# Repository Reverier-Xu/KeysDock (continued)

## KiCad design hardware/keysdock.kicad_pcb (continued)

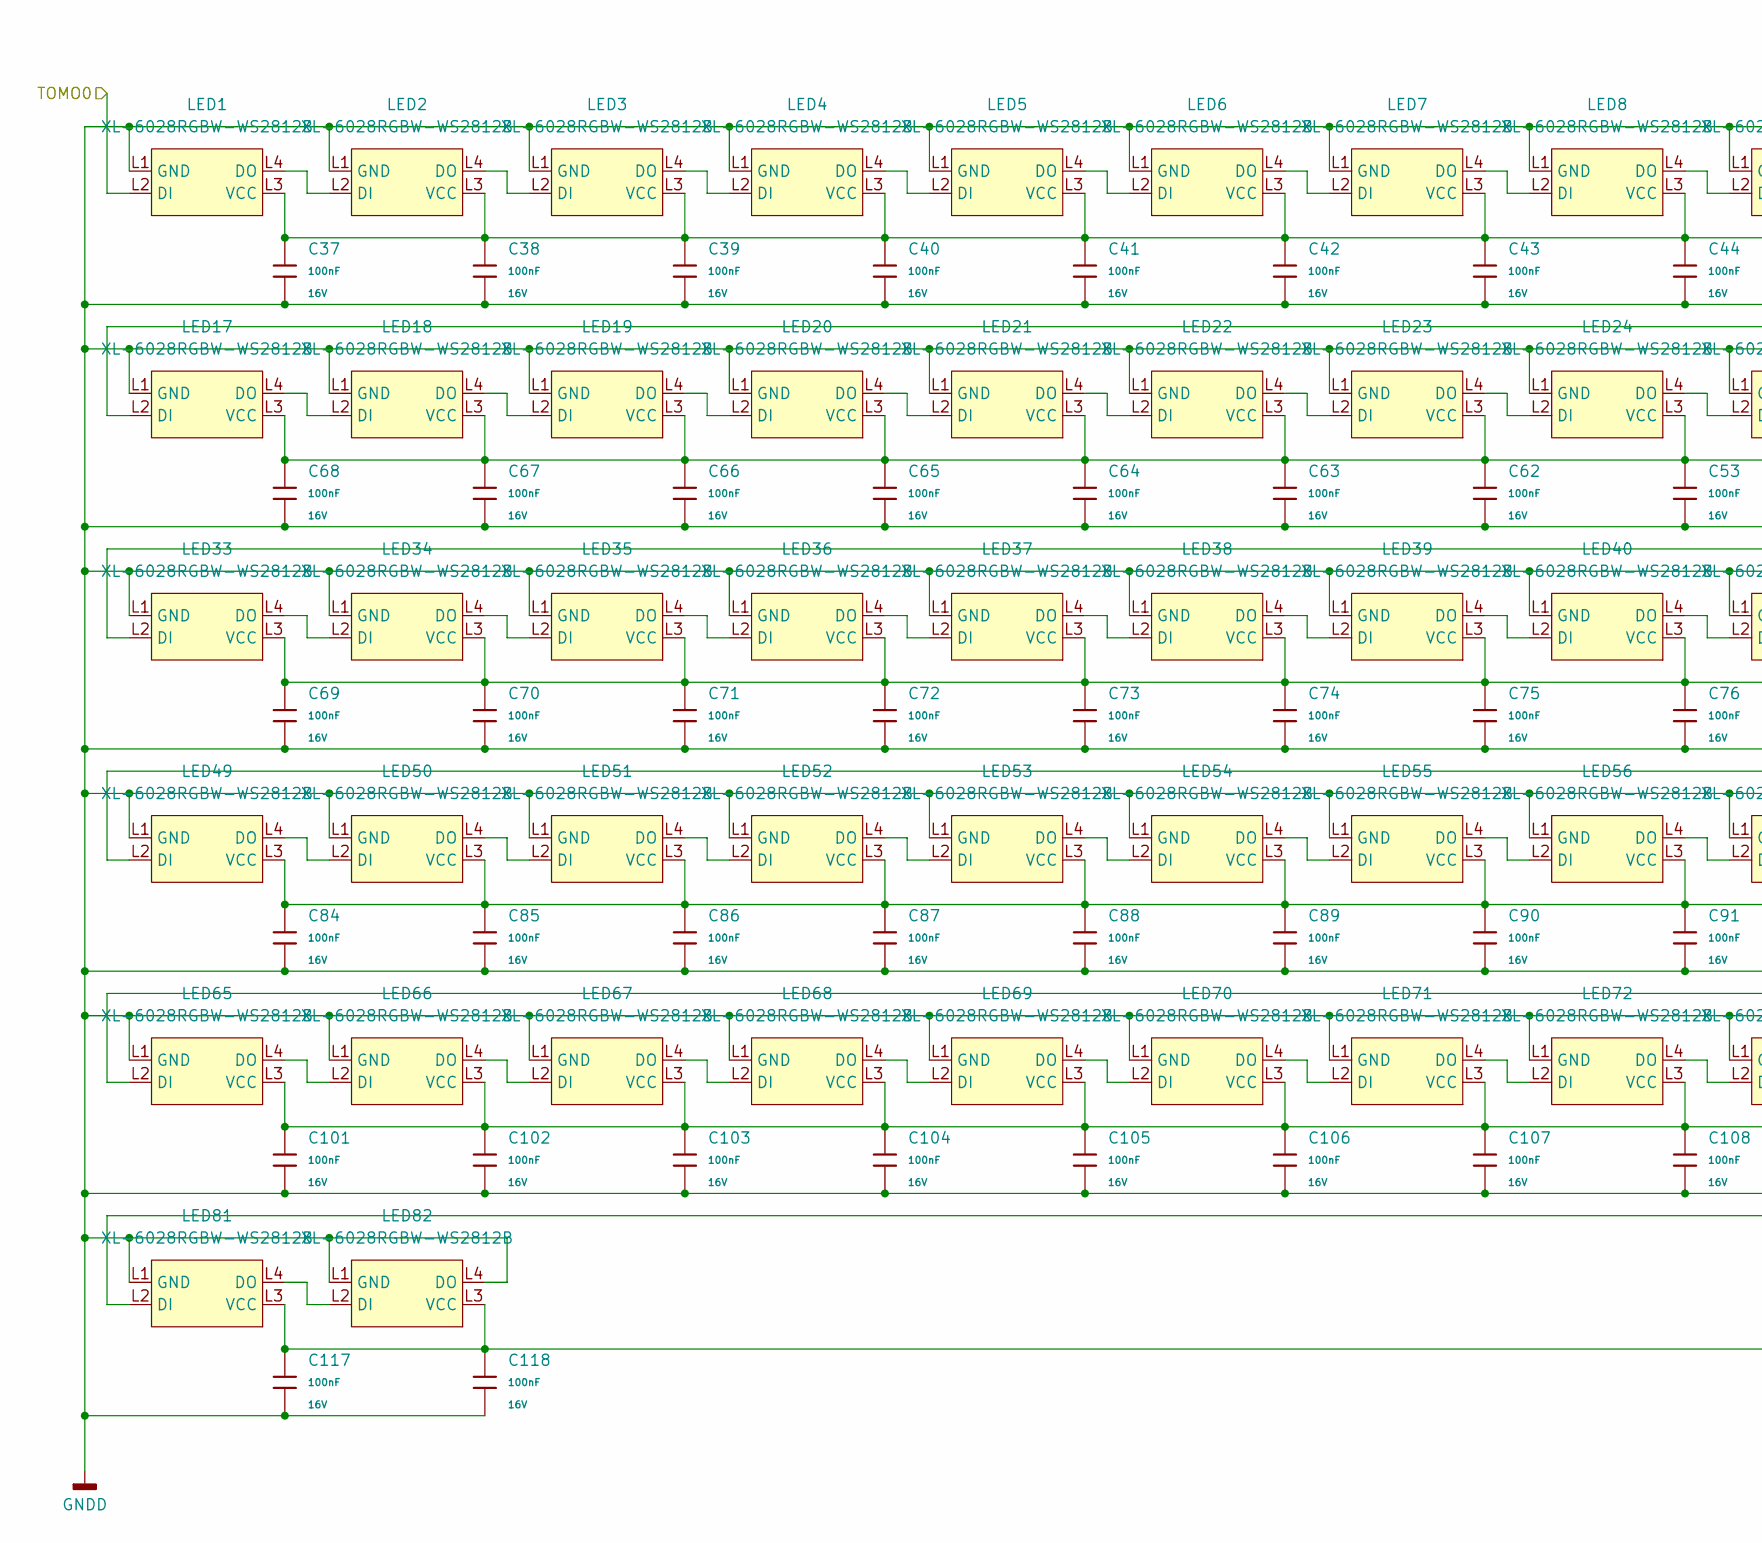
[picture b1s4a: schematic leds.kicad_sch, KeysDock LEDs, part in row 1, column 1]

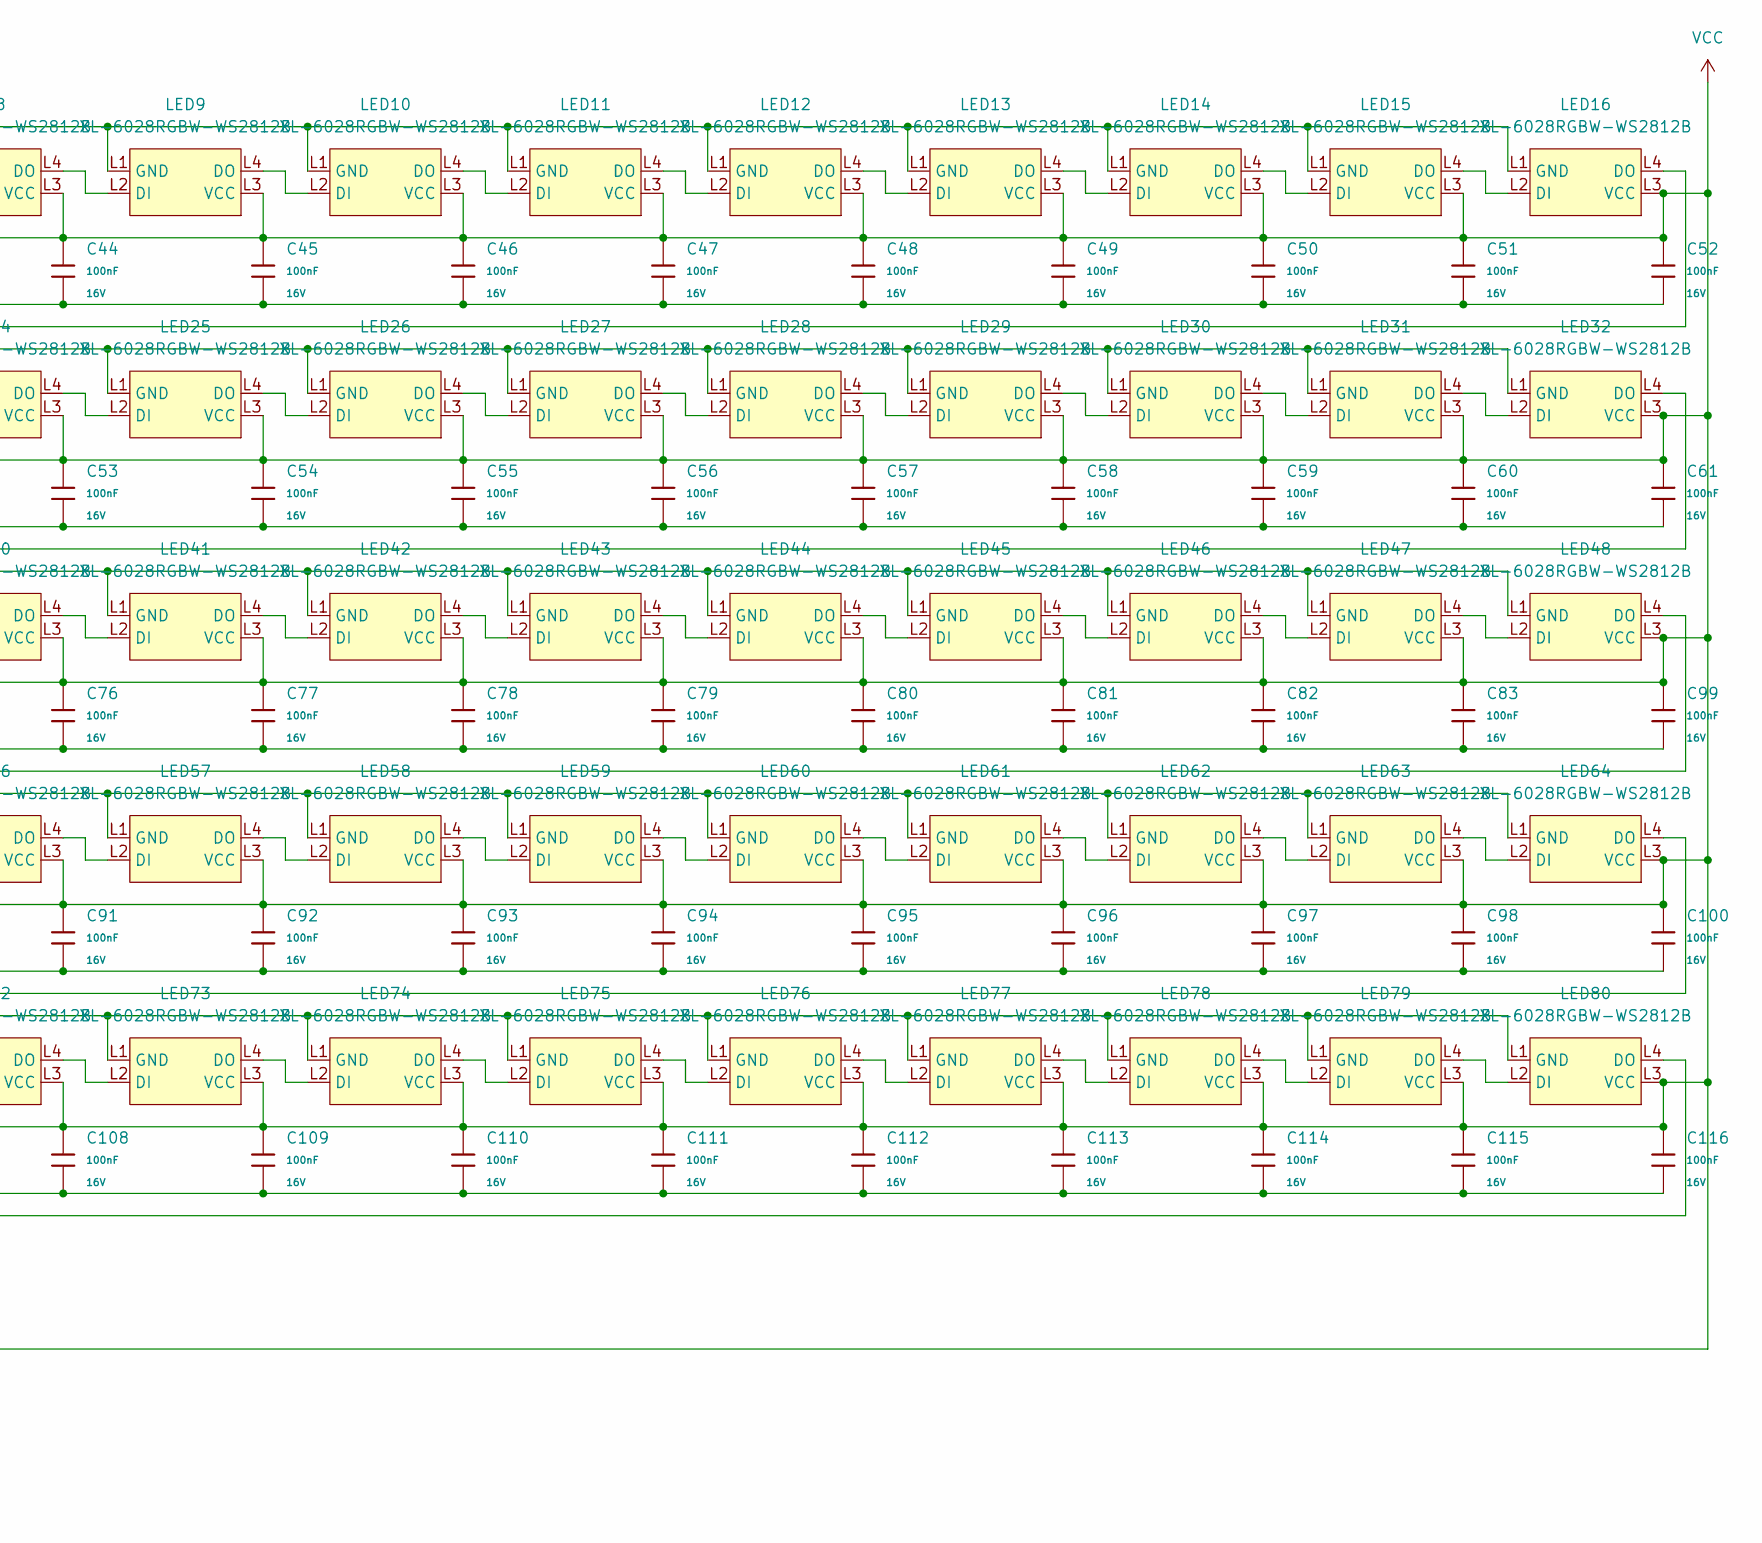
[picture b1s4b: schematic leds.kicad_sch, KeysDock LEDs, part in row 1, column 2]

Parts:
C37, C38, C39, C40, C41, C42, C43, C44, C45, C46, C47, C48, C49, C50, C51, C52, C53, C54, C55, C56, C57, C58, C59, C60, C61, C62, C63, C64, C65, C66, C67, C68, C69, C70, C71, C72, C73, C74, C75, C76, C77, C78, C79, C80, C81, C82, C83, C84, C85, C86, C87, C88, C89, C90, C91, C92, C93, C94, C95, C96, C97, C98, C99, C100, C101, C102, C103, C104, C105, C106, C107, C108, C109, C110, C111, C112, C113, C114, C115, C116, C117, C118: 100nF; C_0402; Voltage Rated 16V; Tolerance ±10%; Part CL05B104KO5NNNC; LCSC C1525
LED1, LED2, LED3, LED4, LED5, LED6, LED7, LED8, LED9, LED10, LED11, LED12, LED13, LED14, LED15, LED16, LED17, LED18, LED19, LED20, LED21, LED22, LED23, LED24, LED25, LED26, LED27, LED28, LED29, LED30, LED31, LED32, LED33, LED34, LED35, LED36, LED37, LED38, LED39, LED40, LED41, LED42, LED43, LED44, LED45, LED46, LED47, LED48, LED49, LED50, LED51, LED52, LED53, LED54, LED55, LED56, LED57, LED58, LED59, LED60, LED61, LED62, LED63, LED64, LED65, LED66, LED67, LED68, LED69, LED70, LED71, LED72, LED73, LED74, LED75, LED76, LED77, LED78, LED79, LED80, LED81, LED82: XL-6028RGBW-WS2812B; LCSC C42163197

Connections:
/leds/TOMO0: LED1.L2 (DI); also elsewhere on the board
GNDD: C37.2, C38.2, C39.2, C40.2, C41.2, C42.2, C43.2, C44.2, C45.2, C46.2, C47.2, C48.2, C49.2, C50.2, C51.2, C52.2, C53.2, C54.2, C55.2, C56.2, C57.2, C58.2, C59.2, C60.2, C61.2, C62.2, C63.2, C64.2, C65.2, C66.2, C67.2, C68.2, C69.2, C70.2, C71.2, C72.2, C73.2, C74.2, C75.2, C76.2, C77.2, C78.2, C79.2, C80.2, C81.2, C82.2, C83.2, C84.2, C85.2, C86.2, C87.2, C88.2, C89.2, C90.2, C91.2, C92.2, C93.2, C94.2, C95.2, C96.2, C97.2, C98.2, C99.2, C100.2, C101.2, C102.2, C103.2, C104.2, C105.2, C106.2, C107.2, C108.2, C109.2, C110.2, C111.2, C112.2, C113.2, C114.2, C115.2, C116.2, C117.2, C118.2, LED1.L1 (GND), LED2.L1 (GND), LED3.L1 (GND), LED4.L1 (GND), LED5.L1 (GND), LED6.L1 (GND), LED7.L1 (GND), LED8.L1 (GND), LED9.L1 (GND), LED10.L1 (GND), LED11.L1 (GND), LED12.L1 (GND), LED13.L1 (GND), LED14.L1 (GND), LED15.L1 (GND), LED16.L1 (GND), LED17.L1 (GND), LED18.L1 (GND), LED19.L1 (GND), LED20.L1 (GND), LED21.L1 (GND), LED22.L1 (GND), LED23.L1 (GND), LED24.L1 (GND), LED25.L1 (GND), LED26.L1 (GND), LED27.L1 (GND), LED28.L1 (GND), LED29.L1 (GND), LED30.L1 (GND), LED31.L1 (GND), LED32.L1 (GND), LED33.L1 (GND), LED34.L1 (GND), LED35.L1 (GND), LED36.L1 (GND), LED37.L1 (GND), LED38.L1 (GND), LED39.L1 (GND), LED40.L1 (GND), LED41.L1 (GND), LED42.L1 (GND), LED43.L1 (GND), LED44.L1 (GND), LED45.L1 (GND), LED46.L1 (GND), LED47.L1 (GND), LED48.L1 (GND), LED49.L1 (GND), LED50.L1 (GND), LED51.L1 (GND), LED52.L1 (GND), LED53.L1 (GND), LED54.L1 (GND), LED55.L1 (GND), LED56.L1 (GND), LED57.L1 (GND), LED58.L1 (GND), LED59.L1 (GND), LED60.L1 (GND), LED61.L1 (GND), LED62.L1 (GND), LED63.L1 (GND), LED64.L1 (GND), LED65.L1 (GND), LED66.L1 (GND), LED67.L1 (GND), LED68.L1 (GND), LED69.L1 (GND), LED70.L1 (GND), LED71.L1 (GND), LED72.L1 (GND), LED73.L1 (GND), LED74.L1 (GND), LED75.L1 (GND), LED76.L1 (GND), LED77.L1 (GND), LED78.L1 (GND), LED79.L1 (GND), LED80.L1 (GND), LED81.L1 (GND), LED82.L1 (GND), LED82.L4 (DO); also elsewhere on the board
unnamed: LED1.L4 (DO), LED2.L2 (DI)
unnamed: LED2.L4 (DO), LED3.L2 (DI)
unnamed: LED3.L4 (DO), LED4.L2 (DI)
unnamed: LED4.L4 (DO), LED5.L2 (DI)
unnamed: LED5.L4 (DO), LED6.L2 (DI)
unnamed: LED6.L4 (DO), LED7.L2 (DI)
unnamed: LED7.L4 (DO), LED8.L2 (DI)
unnamed: LED8.L4 (DO), LED9.L2 (DI)
unnamed: LED9.L4 (DO), LED10.L2 (DI)
unnamed: LED10.L4 (DO), LED11.L2 (DI)
unnamed: LED11.L4 (DO), LED12.L2 (DI)
unnamed: LED12.L4 (DO), LED13.L2 (DI)
unnamed: LED13.L4 (DO), LED14.L2 (DI)
unnamed: LED14.L4 (DO), LED15.L2 (DI)
unnamed: LED15.L4 (DO), LED16.L2 (DI)
unnamed: LED16.L4 (DO), LED17.L2 (DI)
unnamed: LED17.L4 (DO), LED18.L2 (DI)
unnamed: LED18.L4 (DO), LED19.L2 (DI)
unnamed: LED19.L4 (DO), LED20.L2 (DI)
unnamed: LED20.L4 (DO), LED21.L2 (DI)
unnamed: LED21.L4 (DO), LED22.L2 (DI)
unnamed: LED22.L4 (DO), LED23.L2 (DI)
unnamed: LED23.L4 (DO), LED24.L2 (DI)
unnamed: LED24.L4 (DO), LED25.L2 (DI)
unnamed: LED25.L4 (DO), LED26.L2 (DI)
unnamed: LED26.L4 (DO), LED27.L2 (DI)
unnamed: LED27.L4 (DO), LED28.L2 (DI)
unnamed: LED28.L4 (DO), LED29.L2 (DI)
unnamed: LED29.L4 (DO), LED30.L2 (DI)
unnamed: LED30.L4 (DO), LED31.L2 (DI)
unnamed: LED31.L4 (DO), LED32.L2 (DI)
unnamed: LED32.L4 (DO), LED33.L2 (DI)
unnamed: LED33.L4 (DO), LED34.L2 (DI)
unnamed: LED34.L4 (DO), LED35.L2 (DI)
unnamed: LED35.L4 (DO), LED36.L2 (DI)
unnamed: LED36.L4 (DO), LED37.L2 (DI)
unnamed: LED37.L4 (DO), LED38.L2 (DI)
unnamed: LED38.L4 (DO), LED39.L2 (DI)
unnamed: LED39.L4 (DO), LED40.L2 (DI)
unnamed: LED40.L4 (DO), LED41.L2 (DI)
unnamed: LED41.L4 (DO), LED42.L2 (DI)
unnamed: LED42.L4 (DO), LED43.L2 (DI)
unnamed: LED43.L4 (DO), LED44.L2 (DI)
unnamed: LED44.L4 (DO), LED45.L2 (DI)
unnamed: LED45.L4 (DO), LED46.L2 (DI)
unnamed: LED46.L4 (DO), LED47.L2 (DI)
unnamed: LED47.L4 (DO), LED48.L2 (DI)
unnamed: LED48.L4 (DO), LED49.L2 (DI)
unnamed: LED49.L4 (DO), LED50.L2 (DI)
unnamed: LED50.L4 (DO), LED51.L2 (DI)
unnamed: LED51.L4 (DO), LED52.L2 (DI)
unnamed: LED52.L4 (DO), LED53.L2 (DI)
unnamed: LED53.L4 (DO), LED54.L2 (DI)
unnamed: LED54.L4 (DO), LED55.L2 (DI)
unnamed: LED55.L4 (DO), LED56.L2 (DI)
unnamed: LED56.L4 (DO), LED57.L2 (DI)
unnamed: LED57.L4 (DO), LED58.L2 (DI)
unnamed: LED58.L4 (DO), LED59.L2 (DI)
unnamed: LED59.L4 (DO), LED60.L2 (DI)
unnamed: LED60.L4 (DO), LED61.L2 (DI)
unnamed: LED61.L4 (DO), LED62.L2 (DI)
unnamed: LED62.L4 (DO), LED63.L2 (DI)
unnamed: LED63.L4 (DO), LED64.L2 (DI)
unnamed: LED64.L4 (DO), LED65.L2 (DI)
unnamed: LED65.L4 (DO), LED66.L2 (DI)
unnamed: LED66.L4 (DO), LED67.L2 (DI)
unnamed: LED67.L4 (DO), LED68.L2 (DI)
unnamed: LED68.L4 (DO), LED69.L2 (DI)
unnamed: LED69.L4 (DO), LED70.L2 (DI)
unnamed: LED70.L4 (DO), LED71.L2 (DI)
unnamed: LED71.L4 (DO), LED72.L2 (DI)
unnamed: LED72.L4 (DO), LED73.L2 (DI)
unnamed: LED73.L4 (DO), LED74.L2 (DI)
unnamed: LED74.L4 (DO), LED75.L2 (DI)
unnamed: LED75.L4 (DO), LED76.L2 (DI)
unnamed: LED76.L4 (DO), LED77.L2 (DI)
unnamed: LED77.L4 (DO), LED78.L2 (DI)
unnamed: LED78.L4 (DO), LED79.L2 (DI)
unnamed: LED79.L4 (DO), LED80.L2 (DI)
unnamed: LED80.L4 (DO), LED81.L2 (DI)
unnamed: LED81.L4 (DO), LED82.L2 (DI)
VCC: C37.1, C38.1, C39.1, C40.1, C41.1, C42.1, C43.1, C44.1, C45.1, C46.1, C47.1, C48.1, C49.1, C50.1, C51.1, C52.1, C53.1, C54.1, C55.1, C56.1, C57.1, C58.1, C59.1, C60.1, C61.1, C62.1, C63.1, C64.1, C65.1, C66.1, C67.1, C68.1, C69.1, C70.1, C71.1, C72.1, C73.1, C74.1, C75.1, C76.1, C77.1, C78.1, C79.1, C80.1, C81.1, C82.1, C83.1, C84.1, C85.1, C86.1, C87.1, C88.1, C89.1, C90.1, C91.1, C92.1, C93.1, C94.1, C95.1, C96.1, C97.1, C98.1, C99.1, C100.1, C101.1, C102.1, C103.1, C104.1, C105.1, C106.1, C107.1, C108.1, C109.1, C110.1, C111.1, C112.1, C113.1, C114.1, C115.1, C116.1, C117.1, C118.1, LED1.L3 (VCC), LED2.L3 (VCC), LED3.L3 (VCC), LED4.L3 (VCC), LED5.L3 (VCC), LED6.L3 (VCC), LED7.L3 (VCC), LED8.L3 (VCC), LED9.L3 (VCC), LED10.L3 (VCC), LED11.L3 (VCC), LED12.L3 (VCC), LED13.L3 (VCC), LED14.L3 (VCC), LED15.L3 (VCC), LED16.L3 (VCC), LED17.L3 (VCC), LED18.L3 (VCC), LED19.L3 (VCC), LED20.L3 (VCC), LED21.L3 (VCC), LED22.L3 (VCC), LED23.L3 (VCC), LED24.L3 (VCC), LED25.L3 (VCC), LED26.L3 (VCC), LED27.L3 (VCC), LED28.L3 (VCC), LED29.L3 (VCC), LED30.L3 (VCC), LED31.L3 (VCC), LED32.L3 (VCC), LED33.L3 (VCC), LED34.L3 (VCC), LED35.L3 (VCC), LED36.L3 (VCC), LED37.L3 (VCC), LED38.L3 (VCC), LED39.L3 (VCC), LED40.L3 (VCC), LED41.L3 (VCC), LED42.L3 (VCC), LED43.L3 (VCC), LED44.L3 (VCC), LED45.L3 (VCC), LED46.L3 (VCC), LED47.L3 (VCC), LED48.L3 (VCC), LED49.L3 (VCC), LED50.L3 (VCC), LED51.L3 (VCC), LED52.L3 (VCC), LED53.L3 (VCC), LED54.L3 (VCC), LED55.L3 (VCC), LED56.L3 (VCC), LED57.L3 (VCC), LED58.L3 (VCC), LED59.L3 (VCC), LED60.L3 (VCC), LED61.L3 (VCC), LED62.L3 (VCC), LED63.L3 (VCC), LED64.L3 (VCC), LED65.L3 (VCC), LED66.L3 (VCC), LED67.L3 (VCC), LED68.L3 (VCC), LED69.L3 (VCC), LED70.L3 (VCC), LED71.L3 (VCC), LED72.L3 (VCC), LED73.L3 (VCC), LED74.L3 (VCC), LED75.L3 (VCC), LED76.L3 (VCC), LED77.L3 (VCC), LED78.L3 (VCC), LED79.L3 (VCC), LED80.L3 (VCC), LED81.L3 (VCC), LED82.L3 (VCC); also elsewhere on the board

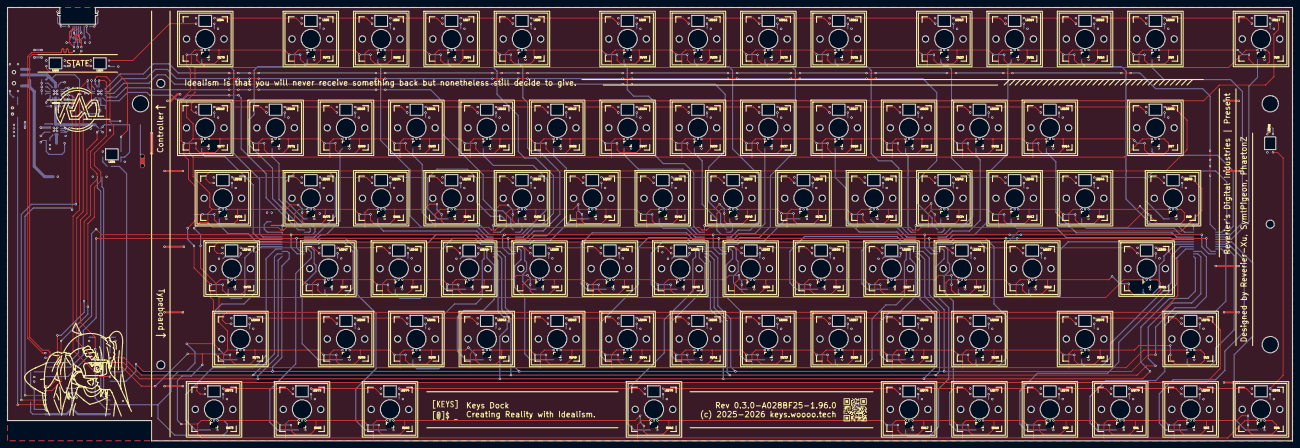
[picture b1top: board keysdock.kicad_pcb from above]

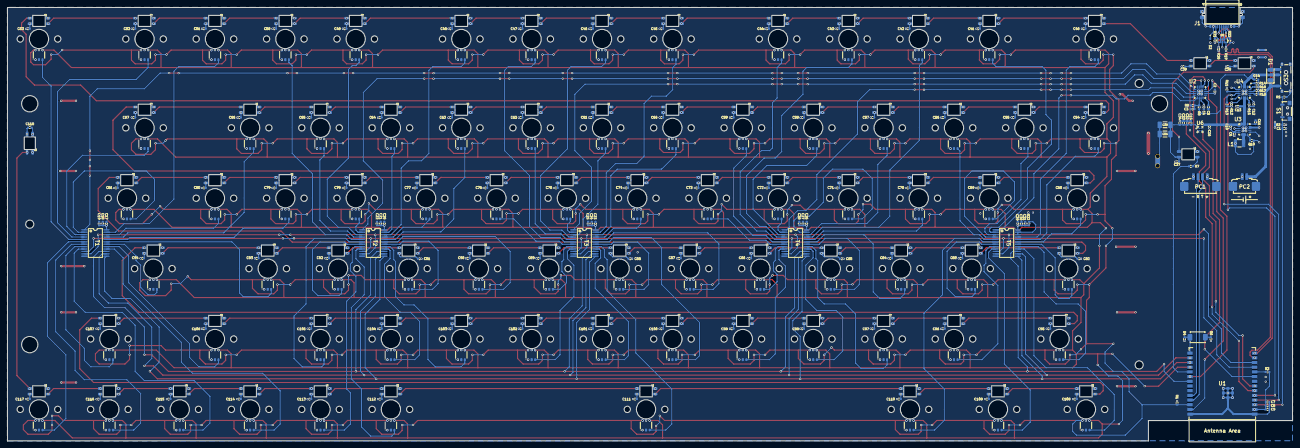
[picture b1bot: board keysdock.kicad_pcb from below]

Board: 4 copper layers, 347.8 x 117.3 mm, 322 parts (161 on the bottom side), 214 nets.

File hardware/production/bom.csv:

Designator,Footprint,Quantity,Value,LCSC Part #
"C1, C12, C15, C2, C32, C4, C5",C_0402,7,1uF,C52923
"C10, C16, C19, C22, C25, C28, C31, C33, C34",C_0402,9,10uF,C15525
"C100, C101, C102, C103, C104, C105, C106, C107, C108, C109, C110, C111, C112, C113, C114, C115, C116, C117, C118, C17, C20, C23, C26, C29, C3, C37, C38, C39, C40, C41, C42, C43, C44, C45, C46, C47, C48, C49, C50, C51, C52, C53, C54, C55, C56, C57, C58, C59, C60, C61, C62, C63, C64, C65, C66, C67, C68, C69, C7, C70, C71, C72, C73, C74, C75, C76, C77, C78, C79, C8, C80, C81, C82, C83, C84, C85, C86, C87, C88, C89, C9, C90, C91, C92, C93, C94, C95, C96, C97, C98, C99",C_0402,91,100nF,C1525
C11,C_0402,1,3.3nF,C26404
"C13, C14, C18, C21, C24, C27, C30",C_0402,7,4.7uF,C23733
"C35, C36",C_1206,2,100uF,C15008
C6,C_0402,1,22uF,C105226
D1,D_SOD-123FL,1,SM4007PL,C78741
D2,DIO_TPD1E05U06DPYR,1,TPD1E10B06DPYR,C48260
J1,USB-C-SMD_SHOUHAN_TYPE-C-16PFS-2JCB1.2-H6.5,1,TYPE-C 16PFS 2JCB1.2-H6.5 IPX8,C3020046
L1,IND-SMD_L2.5-W2.0_MHCHL2520,1,2.2uH,C5832372
"LED1, LED10, LED11, LED12, LED13, LED14, LED15, LED16, LED17, LED18, LED19, LED2, LED20, LED21, LED22, LED23, LED24, LED25, LED26, LED27, LED28, LED29, LED3, LED30, LED31, LED32, LED33, LED34, LED35, LED36, LED37, LED38, LED39, LED4, LED40, LED41, LED42, LED43, LED44, LED45, LED46, LED47, LED48, LED49, LED5, LED50, LED51, LED52, LED53, LED54, LED55, LED56, LED57, LED58, LED59, LED6, LED60, LED61, LED62, LED63, LED64, LED65, LED66, LED67, LED68, LED69, LED7, LED70, LED71, LED72, LED73, LED74, LED75, LED76, LED77, LED78, LED79, LED8, LED80, LED81, LED82, LED9",XL-6028RGBW-WS2812B,82,XL-6028RGBW-WS2812B,C42163197
PC1,HC-1.25-4PWT,1,HC-1.25-4PWT,C2845381
PC2,HC-1.25-2PWT,1,HC-1.25-2PWT,C2845379
"R1, R11, R14, R2, R23, R3, R4",R_0402,7,10kΩ,C25744
"R10, R8, R9",R_0402,3,100kΩ,C25741
"R12, R13",R_0402,2,1.5kΩ,C25867
R15,R_0402,1,1.10kΩ,C25860
R16,R_0402,1,47kΩ,C25792
R17,R_0402,1,3kΩ,C25784
R18,R_0402,1,750Ω,C25132
"R19, R20",R_0402,2,22Ω,C25092
"R21, R22",R_0402,2,5.1kΩ,C25941
"R5, R6",R_0402,2,100Ω,C25076
R7,R_0402,1,499Ω,C4125
S1,TS24CA,1,TS24CA,C393942
S2,SW_TS-1088-AR02016,1,"TS-1088-AR02016, 160gf",C720477
S3,SW-SMD_SSSS811101,1,SSSS811101,C109335
"SW1, SW10, SW11, SW12, SW13, SW14, SW15, SW16, SW17, SW18, SW19, SW2, SW20, SW21, SW22, SW23, SW24, SW25, SW26, SW27, SW28, SW29, SW3, SW30, SW31, SW32, SW33, SW34, SW35, SW36, SW37, SW38, SW39, SW4, SW40, SW41, SW42, SW43, SW44, SW45, SW46, SW47, SW48, SW49, SW5, SW50, SW51, SW52, SW53, SW54, SW55, SW56, SW57, SW58, SW59, SW6, SW60, SW61, SW62, SW63, SW64, SW65, SW66, SW67, SW68, SW69, SW7, SW70, SW71, SW72, SW73, SW74, SW75, SW76, SW77, SW78, SW8, SW9",KD-SINGLE-KEY,78,SC4823S6-TR,C52021064
"T1, T2, T3, T4, T5",XL4067TS,5,XL4067TS,C41427445
U1,ESP32-C6-WROOM-1,1,ESP32-C6-WROOM-1-N8,
U2,QFN50P300X300X80-17N,1,TLA2518IRTER,C1855741
U3,QFN50P300X300X80-17N,1,TPS62142RGTR,C129331
U4,QFN50P300X300X80-17N,1,BQ24074RGTR,C54313
U5,IC_TPD4E05U06DQAR,1,TPD4E05U06DQAR,C138714
U6,BGA4N50P2X2_88X88X50N,1,TPS22910AYZVR,C205966
